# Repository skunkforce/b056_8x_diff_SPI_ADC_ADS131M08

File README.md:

# edgy_board number b056
This design is part of the [edgy board project](https://github.com/skunkforce/edgy_boards). It provides an 8x diff ADC using ADS131M08. 

# getting started
This repository uses submodules. After cloning use the command 

```$ git submodule update --init --recursive```

to pull the submodules before opening the project with kicad. 

# Tests
Tests can be found in [TESTS.md](TESTS.md)

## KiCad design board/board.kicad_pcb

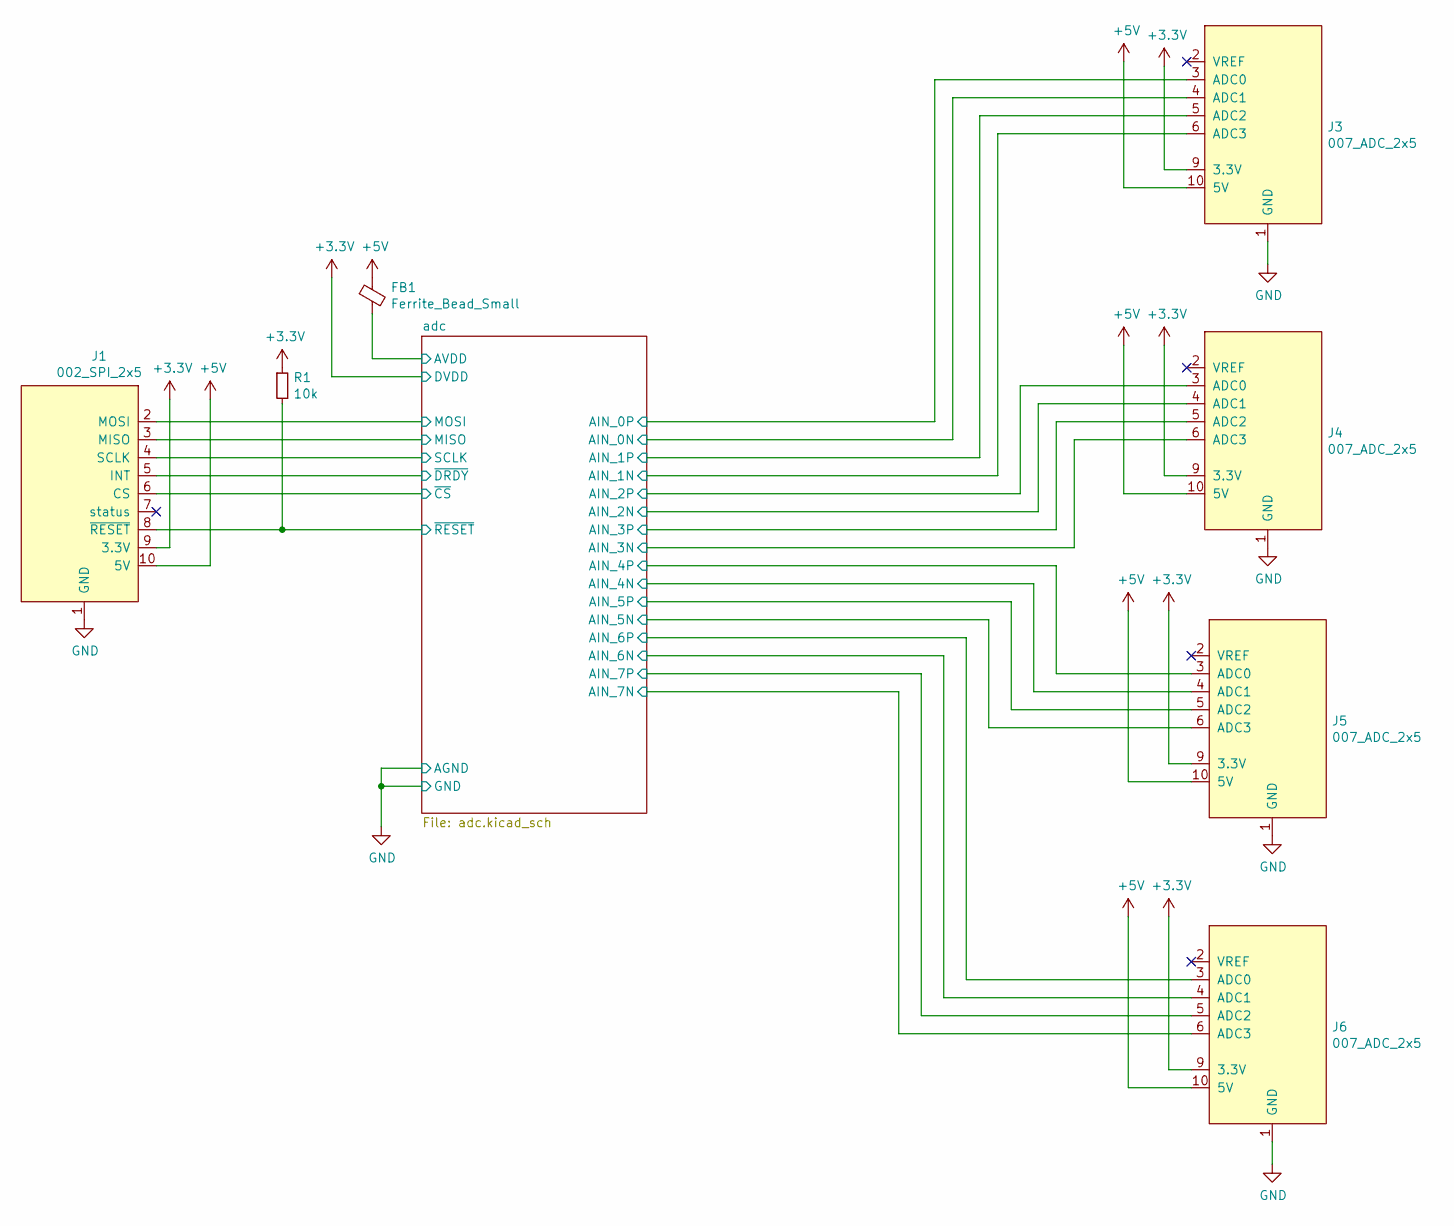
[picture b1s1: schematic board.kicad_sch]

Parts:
FB1: Ferrite_Bead_Small; L_0603_1608Metric
J1: 002_SPI_2x5; on_edge_2x05_device
J3, J4, J5, J6: 007_ADC_2x5; on_edge_2x05_host
R1: 10k; R_0603_1608Metric

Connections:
+3.3V: J1.9 (3.3V), J3.9 (3.3V), J4.9 (3.3V), J5.9 (3.3V), J6.9 (3.3V), R1.1; also elsewhere on the board
+5V: FB1.1, J1.10 (5V), J3.10 (5V), J4.10 (5V), J5.10 (5V), J6.10 (5V)
/adc/AIN_0N: J3.4 (ADC1); also elsewhere on the board
/adc/AIN_0P: J3.3 (ADC0); also elsewhere on the board
/adc/AIN_1N: J3.6 (ADC3); also elsewhere on the board
/adc/AIN_1P: J3.5 (ADC2); also elsewhere on the board
/adc/AIN_2N: J4.4 (ADC1); also elsewhere on the board
/adc/AIN_2P: J4.3 (ADC0); also elsewhere on the board
/adc/AIN_3N: J4.6 (ADC3); also elsewhere on the board
/adc/AIN_3P: J4.5 (ADC2); also elsewhere on the board
/adc/AIN_4N: J5.4 (ADC1); also elsewhere on the board
/adc/AIN_4P: J5.3 (ADC0); also elsewhere on the board
/adc/AIN_5N: J5.6 (ADC3); also elsewhere on the board
/adc/AIN_5P: J5.5 (ADC2); also elsewhere on the board
/adc/AIN_6N: J6.4 (ADC1); also elsewhere on the board
/adc/AIN_6P: J6.3 (ADC0); also elsewhere on the board
/adc/AIN_7N: J6.6 (ADC3); also elsewhere on the board
/adc/AIN_7P: J6.5 (ADC2); also elsewhere on the board
/adc/AVDD: FB1.2; also elsewhere on the board
/adc/MISO: J1.3 (MISO); also elsewhere on the board
/adc/MOSI: J1.2 (MOSI); also elsewhere on the board
/adc/SCLK: J1.4 (SCLK); also elsewhere on the board
/adc/~CS: J1.6 (CS); also elsewhere on the board
/adc/~DRDY: J1.5 (INT); also elsewhere on the board
/adc/~RESET: J1.8 (~RESET), R1.2; also elsewhere on the board
GND: J1.1 (GND), J3.1 (GND), J4.1 (GND), J5.1 (GND), J6.1 (GND); also elsewhere on the board

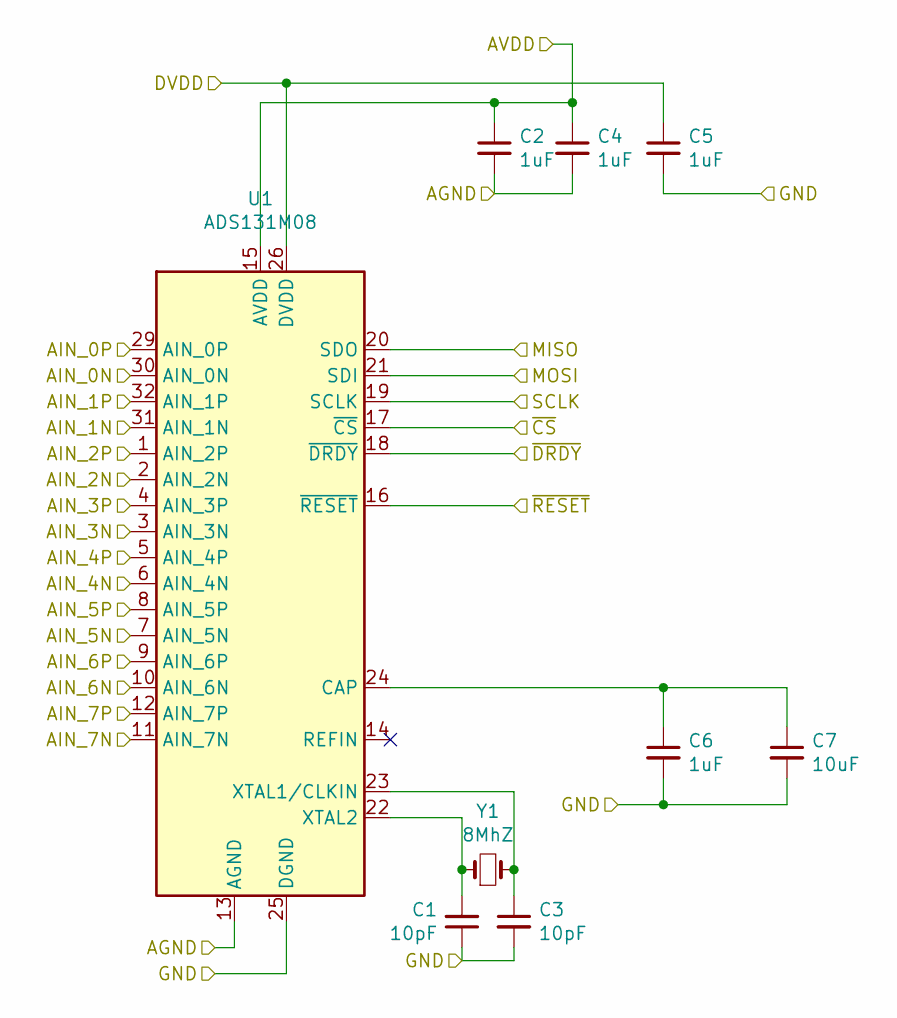
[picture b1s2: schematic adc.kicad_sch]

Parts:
C1, C3: 10pF; C_0603_1608Metric
C2, C4, C5, C6: 1uF; C_0603_1608Metric
C7: 10uF; C_0603_1608Metric
U1: ADS131M08; QFN-32-1EP_4x4mm_P0.4mm_EP2.9x2.9mm
Y1: 8MhZ; Crystal_SMD_5032-2Pin_5.0x3.2mm

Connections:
+3.3V: C5.1, U1.26 (DVDD); also elsewhere on the board
/adc/AIN_0N: U1.30 (AIN_0N); also elsewhere on the board
/adc/AIN_0P: U1.29 (AIN_0P); also elsewhere on the board
/adc/AIN_1N: U1.31 (AIN_1N); also elsewhere on the board
/adc/AIN_1P: U1.32 (AIN_1P); also elsewhere on the board
/adc/AIN_2N: U1.2 (AIN_2N); also elsewhere on the board
/adc/AIN_2P: U1.1 (AIN_2P); also elsewhere on the board
/adc/AIN_3N: U1.3 (AIN_3N); also elsewhere on the board
/adc/AIN_3P: U1.4 (AIN_3P); also elsewhere on the board
/adc/AIN_4N: U1.6 (AIN_4N); also elsewhere on the board
/adc/AIN_4P: U1.5 (AIN_4P); also elsewhere on the board
/adc/AIN_5N: U1.7 (AIN_5N); also elsewhere on the board
/adc/AIN_5P: U1.8 (AIN_5P); also elsewhere on the board
/adc/AIN_6N: U1.10 (AIN_6N); also elsewhere on the board
/adc/AIN_6P: U1.9 (AIN_6P); also elsewhere on the board
/adc/AIN_7N: U1.11 (AIN_7N); also elsewhere on the board
/adc/AIN_7P: U1.12 (AIN_7P); also elsewhere on the board
/adc/AVDD: C2.1, C4.1, U1.15 (AVDD); also elsewhere on the board
/adc/MISO: U1.20 (SDO); also elsewhere on the board
/adc/MOSI: U1.21 (SDI); also elsewhere on the board
/adc/SCLK: U1.19 (SCLK); also elsewhere on the board
/adc/~CS: U1.17 (~CS); also elsewhere on the board
/adc/~DRDY: U1.18 (~DRDY); also elsewhere on the board
/adc/~RESET: U1.16 (~RESET); also elsewhere on the board
GND: C1.1, C2.2, C3.2, C4.2, C5.2, C6.2, C7.2, U1.13 (AGND), U1.25 (DGND), U1.28 (AGND), U1.33 (AGND); also elsewhere on the board
unnamed: C1.2, U1.22 (XTAL2), Y1.1
unnamed: C3.1, U1.23 (XTAL1/CLKIN), Y1.2
unnamed: C6.1, C7.1, U1.24 (CAP)

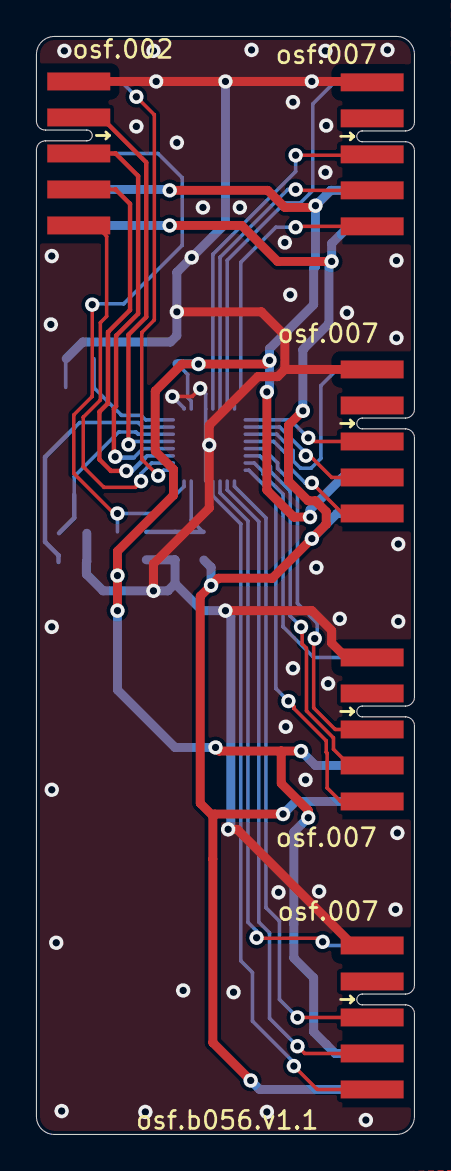
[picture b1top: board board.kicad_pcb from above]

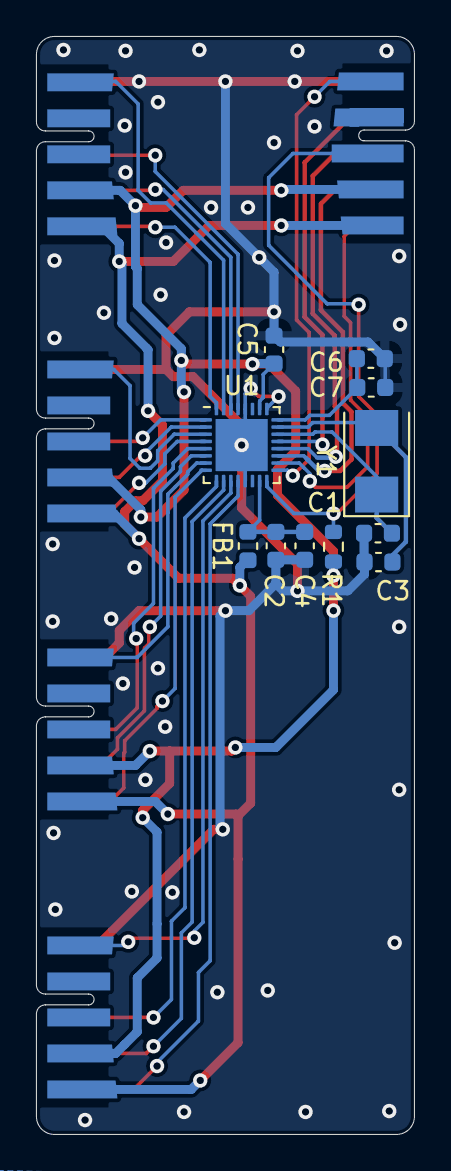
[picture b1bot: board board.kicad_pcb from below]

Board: 2 copper layers, 21.0 x 61.0 mm, 16 parts (11 on the bottom side), 29 nets.

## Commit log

2023-03-11 initial
2023-03-19 separated gnd and agnd
2023-04-28 Changed adc footprint
    ADC footprint was qfn 5x5 but the package is qfn 4x4.
2023-05-02 fixed footprint and added pours
